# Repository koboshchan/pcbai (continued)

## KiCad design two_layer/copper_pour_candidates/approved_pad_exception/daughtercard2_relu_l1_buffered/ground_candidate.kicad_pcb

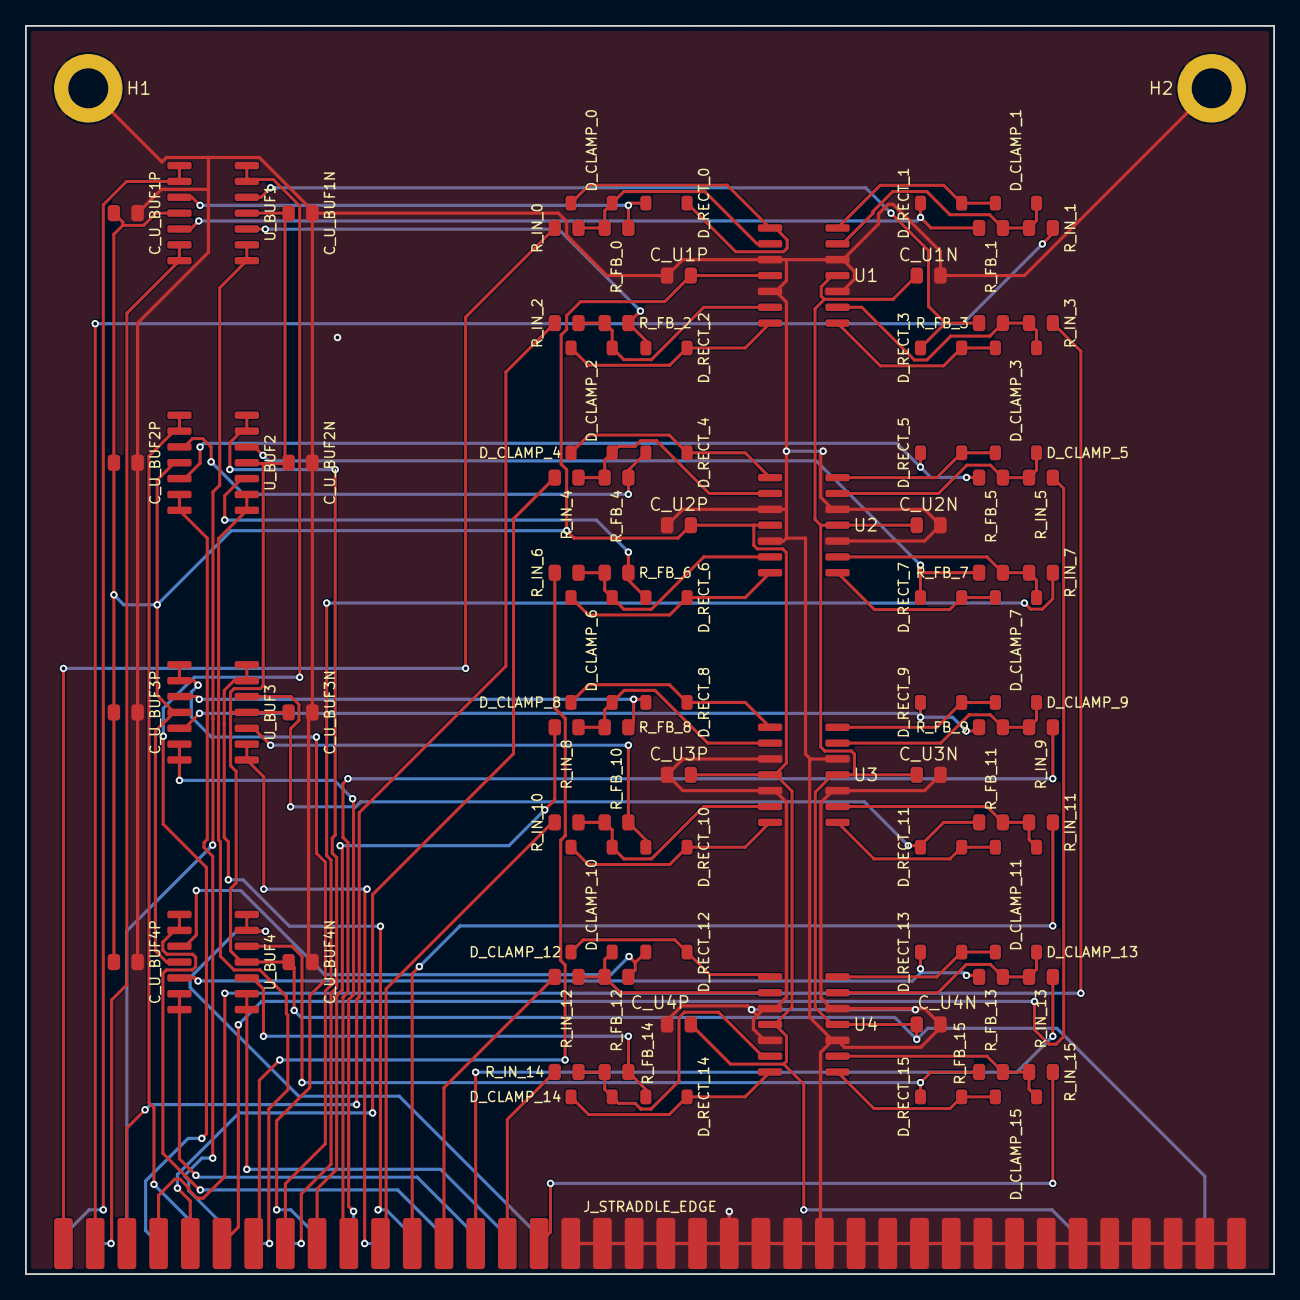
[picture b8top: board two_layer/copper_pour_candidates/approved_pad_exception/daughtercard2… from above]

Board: 2 copper layers, 100.0 x 100.0 mm, 91 parts (0 on the bottom side), 83 nets.

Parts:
C_U1N, C_U1P, C_U2N, C_U2P, C_U3N, C_U3P, C_U4N, C_U4P: 0.1uF; C_0805_2012Metric
C_U_BUF1N, C_U_BUF1P, C_U_BUF2N, C_U_BUF2P, C_U_BUF3N, C_U_BUF3P, C_U_BUF4N, C_U_BUF4P: 0.1uF; C_0805_2012Metric
D_CLAMP_0, D_CLAMP_1, D_CLAMP_2, D_CLAMP_3, D_CLAMP_4, D_CLAMP_5, D_CLAMP_6, D_CLAMP_7, D_CLAMP_8, D_CLAMP_9, D_CLAMP_10, D_CLAMP_11, D_CLAMP_12, D_CLAMP_13, D_CLAMP_14, D_CLAMP_15: 1N4148W; D_SOD-123
D_RECT_0, D_RECT_1, D_RECT_2, D_RECT_3, D_RECT_4, D_RECT_5, D_RECT_6, D_RECT_7, D_RECT_8, D_RECT_9, D_RECT_10, D_RECT_11, D_RECT_12, D_RECT_13, D_RECT_14, D_RECT_15: 1N4148W; D_SOD-123
H1, H2: MountingHole; MountingHole_3.2mm_M3_Pad
J_STRADDLE_EDGE: PinHeader_2x38_Straddle; PinHeader_2x38_Straddle_P2.54mm
R_FB_0, R_FB_1, R_FB_2, R_FB_3, R_FB_4, R_FB_5, R_FB_6, R_FB_7, R_FB_8, R_FB_9, R_FB_10, R_FB_11, R_FB_12, R_FB_13, R_FB_14, R_FB_15: 10k; R_0805_2012Metric
R_IN_0, R_IN_1, R_IN_2, R_IN_3, R_IN_4, R_IN_5, R_IN_6, R_IN_7, R_IN_8, R_IN_9, R_IN_10, R_IN_11, R_IN_12, R_IN_13, R_IN_14, R_IN_15: 10k; R_0805_2012Metric
U1, U2, U3, U4: TL074; SOIC-14_3.9x8.7mm_P1.27mm
U_BUF1, U_BUF2, U_BUF3, U_BUF4: TL074; SOIC-14_3.9x8.7mm_P1.27mm

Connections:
+15V: C_U1P.2, C_U2P.2, C_U3P.2, C_U4P.2, C_U_BUF1P.1, C_U_BUF2P.1, C_U_BUF3P.1, C_U_BUF4P.1, J_STRADDLE_EDGE.B33, J_STRADDLE_EDGE.B34, U1.4, U2.4, U3.4, U4.4, U_BUF1.4, U_BUF2.4, U_BUF3.4, U_BUF4.4
-15V: C_U1N.1, C_U2N.1, C_U3N.1, C_U4N.1, C_U_BUF1N.1, C_U_BUF2N.1, C_U_BUF3N.1, C_U_BUF4N.1, J_STRADDLE_EDGE.B37, J_STRADDLE_EDGE.B38, U1.11, U2.11, U3.11, U4.11, U_BUF1.11, U_BUF2.11, U_BUF3.11, U_BUF4.11
ACT_0: J_STRADDLE_EDGE.B1, U_BUF1.1, U_BUF1.2
ACT_1: J_STRADDLE_EDGE.B2, U_BUF1.6, U_BUF1.7
ACT_2: J_STRADDLE_EDGE.B3, U_BUF1.8, U_BUF1.9
ACT_3: J_STRADDLE_EDGE.B4, U_BUF1.13, U_BUF1.14
ACT_4: J_STRADDLE_EDGE.B5, U_BUF2.1, U_BUF2.2
ACT_5: J_STRADDLE_EDGE.B6, U_BUF2.6, U_BUF2.7
ACT_6: J_STRADDLE_EDGE.B7, U_BUF2.8, U_BUF2.9
ACT_7: J_STRADDLE_EDGE.B8, U_BUF2.13, U_BUF2.14
ACT_8: J_STRADDLE_EDGE.B9, U_BUF3.1, U_BUF3.2
ACT_9: J_STRADDLE_EDGE.B10, U_BUF3.6, U_BUF3.7
ACT_10: J_STRADDLE_EDGE.B11, U_BUF3.8, U_BUF3.9
ACT_11: J_STRADDLE_EDGE.B12, U_BUF3.13, U_BUF3.14
ACT_12: J_STRADDLE_EDGE.B13, U_BUF4.1, U_BUF4.2
ACT_13: J_STRADDLE_EDGE.B14, U_BUF4.6, U_BUF4.7
ACT_14: J_STRADDLE_EDGE.B15, U_BUF4.8, U_BUF4.9
ACT_15: J_STRADDLE_EDGE.B16, U_BUF4.13, U_BUF4.14
GND: C_U1N.2, C_U1P.1, C_U2N.2, C_U2P.1, C_U3N.2, C_U3P.1, C_U4N.2, C_U4P.1, C_U_BUF1N.2, C_U_BUF1P.2, C_U_BUF2N.2, C_U_BUF2P.2, C_U_BUF3N.2, C_U_BUF3P.2, C_U_BUF4N.2, C_U_BUF4P.2, H1.1, H2.1, J_STRADDLE_EDGE.A17, J_STRADDLE_EDGE.A18, J_STRADDLE_EDGE.A19, J_STRADDLE_EDGE.A20, J_STRADDLE_EDGE.A21, J_STRADDLE_EDGE.A22, J_STRADDLE_EDGE.A23, J_STRADDLE_EDGE.A24, J_STRADDLE_EDGE.A25, J_STRADDLE_EDGE.A26, J_STRADDLE_EDGE.A27, J_STRADDLE_EDGE.A28, J_STRADDLE_EDGE.A29, J_STRADDLE_EDGE.A30, J_STRADDLE_EDGE.A31, J_STRADDLE_EDGE.A32, J_STRADDLE_EDGE.A33, J_STRADDLE_EDGE.A34, J_STRADDLE_EDGE.A35, J_STRADDLE_EDGE.A36, J_STRADDLE_EDGE.A37, J_STRADDLE_EDGE.A38, J_STRADDLE_EDGE.B17, J_STRADDLE_EDGE.B18, J_STRADDLE_EDGE.B19, J_STRADDLE_EDGE.B20, J_STRADDLE_EDGE.B21, J_STRADDLE_EDGE.B22, J_STRADDLE_EDGE.B23, J_STRADDLE_EDGE.B24, J_STRADDLE_EDGE.B25, J_STRADDLE_EDGE.B26, J_STRADDLE_EDGE.B27, J_STRADDLE_EDGE.B28, J_STRADDLE_EDGE.B29, J_STRADDLE_EDGE.B30, J_STRADDLE_EDGE.B31, J_STRADDLE_EDGE.B32, U1.3, U1.5, U1.10, U1.12, U2.3, U2.5, U2.10, U2.12, U3.3, U3.5, U3.10, U3.12, U4.3, U4.5, U4.10, U4.12
INV_RELU_0: D_CLAMP_0.2, R_FB_0.1, R_IN_0.2, U1.2
INV_RELU_1: D_CLAMP_1.2, R_FB_1.2, R_IN_1.1, U1.13
INV_RELU_2: D_CLAMP_2.2, R_FB_2.1, R_IN_2.2, U1.6
INV_RELU_3: D_CLAMP_3.2, R_FB_3.2, R_IN_3.1, U1.9
INV_RELU_4: D_CLAMP_4.2, R_FB_4.1, R_IN_4.2, U2.2
INV_RELU_5: D_CLAMP_5.2, R_FB_5.2, R_IN_5.1, U2.13
INV_RELU_6: D_CLAMP_6.2, R_FB_6.1, R_IN_6.2, U2.6
INV_RELU_7: D_CLAMP_7.2, R_FB_7.2, R_IN_7.1, U2.9
INV_RELU_8: D_CLAMP_8.2, R_FB_8.1, R_IN_8.2, U3.2
INV_RELU_9: D_CLAMP_9.2, R_FB_9.2, R_IN_9.1, U3.13
INV_RELU_10: D_CLAMP_10.2, R_FB_10.1, R_IN_10.2, U3.6
INV_RELU_11: D_CLAMP_11.2, R_FB_11.2, R_IN_11.1, U3.9
INV_RELU_12: D_CLAMP_12.2, R_FB_12.1, R_IN_12.2, U4.2
INV_RELU_13: D_CLAMP_13.2, R_FB_13.2, R_IN_13.1, U4.13
INV_RELU_14: D_CLAMP_14.2, R_FB_14.1, R_IN_14.2, U4.6
INV_RELU_15: D_CLAMP_15.2, R_FB_15.2, R_IN_15.1, U4.9
OP_OUT_0: D_CLAMP_0.1, D_RECT_0.2, U1.1
OP_OUT_1: D_CLAMP_1.1, D_RECT_1.2, U1.14
OP_OUT_2: D_CLAMP_2.1, D_RECT_2.2, U1.7
OP_OUT_3: D_CLAMP_3.1, D_RECT_3.2, U1.8
OP_OUT_4: D_CLAMP_4.1, D_RECT_4.2, U2.1
OP_OUT_5: D_CLAMP_5.1, D_RECT_5.2, U2.14
OP_OUT_6: D_CLAMP_6.1, D_RECT_6.2, U2.7
OP_OUT_7: D_CLAMP_7.1, D_RECT_7.2, U2.8
OP_OUT_8: D_CLAMP_8.1, D_RECT_8.2, U3.1
OP_OUT_9: D_CLAMP_9.1, D_RECT_9.2, U3.14
OP_OUT_10: D_CLAMP_10.1, D_RECT_10.2, U3.7
OP_OUT_11: D_CLAMP_11.1, D_RECT_11.2, U3.8
OP_OUT_12: D_CLAMP_12.1, D_RECT_12.2, U4.1
OP_OUT_13: D_CLAMP_13.1, D_RECT_13.2, U4.14
OP_OUT_14: D_CLAMP_14.1, D_RECT_14.2, U4.7
OP_OUT_15: D_CLAMP_15.1, D_RECT_15.2, U4.8
RECT_0: D_RECT_0.1, R_FB_0.2, U_BUF1.3
RECT_1: D_RECT_1.1, R_FB_1.1, U_BUF1.5
RECT_2: D_RECT_2.1, R_FB_2.2, U_BUF1.10
RECT_3: D_RECT_3.1, R_FB_3.1, U_BUF1.12
RECT_4: D_RECT_4.1, R_FB_4.2, U_BUF2.3
RECT_5: D_RECT_5.1, R_FB_5.1, U_BUF2.5
RECT_6: D_RECT_6.1, R_FB_6.2, U_BUF2.10
RECT_7: D_RECT_7.1, R_FB_7.1, U_BUF2.12
RECT_8: D_RECT_8.1, R_FB_8.2, U_BUF3.3
RECT_9: D_RECT_9.1, R_FB_9.1, U_BUF3.5
RECT_10: D_RECT_10.1, R_FB_10.2, U_BUF3.10
RECT_11: D_RECT_11.1, R_FB_11.1, U_BUF3.12
RECT_12: D_RECT_12.1, R_FB_12.2, U_BUF4.3
RECT_13: D_RECT_13.1, R_FB_13.1, U_BUF4.5
RECT_14: D_RECT_14.1, R_FB_14.2, U_BUF4.10
RECT_15: D_RECT_15.1, R_FB_15.1, U_BUF4.12
V_SUM_0: J_STRADDLE_EDGE.A1, R_IN_0.1
V_SUM_1: J_STRADDLE_EDGE.A2, R_IN_1.2
V_SUM_2: J_STRADDLE_EDGE.A3, R_IN_2.1
V_SUM_3: J_STRADDLE_EDGE.A4, R_IN_3.2
V_SUM_4: J_STRADDLE_EDGE.A5, R_IN_4.1
V_SUM_5: J_STRADDLE_EDGE.A6, R_IN_5.2
V_SUM_6: J_STRADDLE_EDGE.A7, R_IN_6.1
V_SUM_7: J_STRADDLE_EDGE.A8, R_IN_7.2
V_SUM_8: J_STRADDLE_EDGE.A9, R_IN_8.1
V_SUM_9: J_STRADDLE_EDGE.A10, R_IN_9.2
V_SUM_10: J_STRADDLE_EDGE.A11, R_IN_10.1
V_SUM_11: J_STRADDLE_EDGE.A12, R_IN_11.2
V_SUM_12: J_STRADDLE_EDGE.A13, R_IN_12.1
V_SUM_13: J_STRADDLE_EDGE.A14, R_IN_13.2
V_SUM_14: J_STRADDLE_EDGE.A15, R_IN_14.1
V_SUM_15: J_STRADDLE_EDGE.A16, R_IN_15.2
